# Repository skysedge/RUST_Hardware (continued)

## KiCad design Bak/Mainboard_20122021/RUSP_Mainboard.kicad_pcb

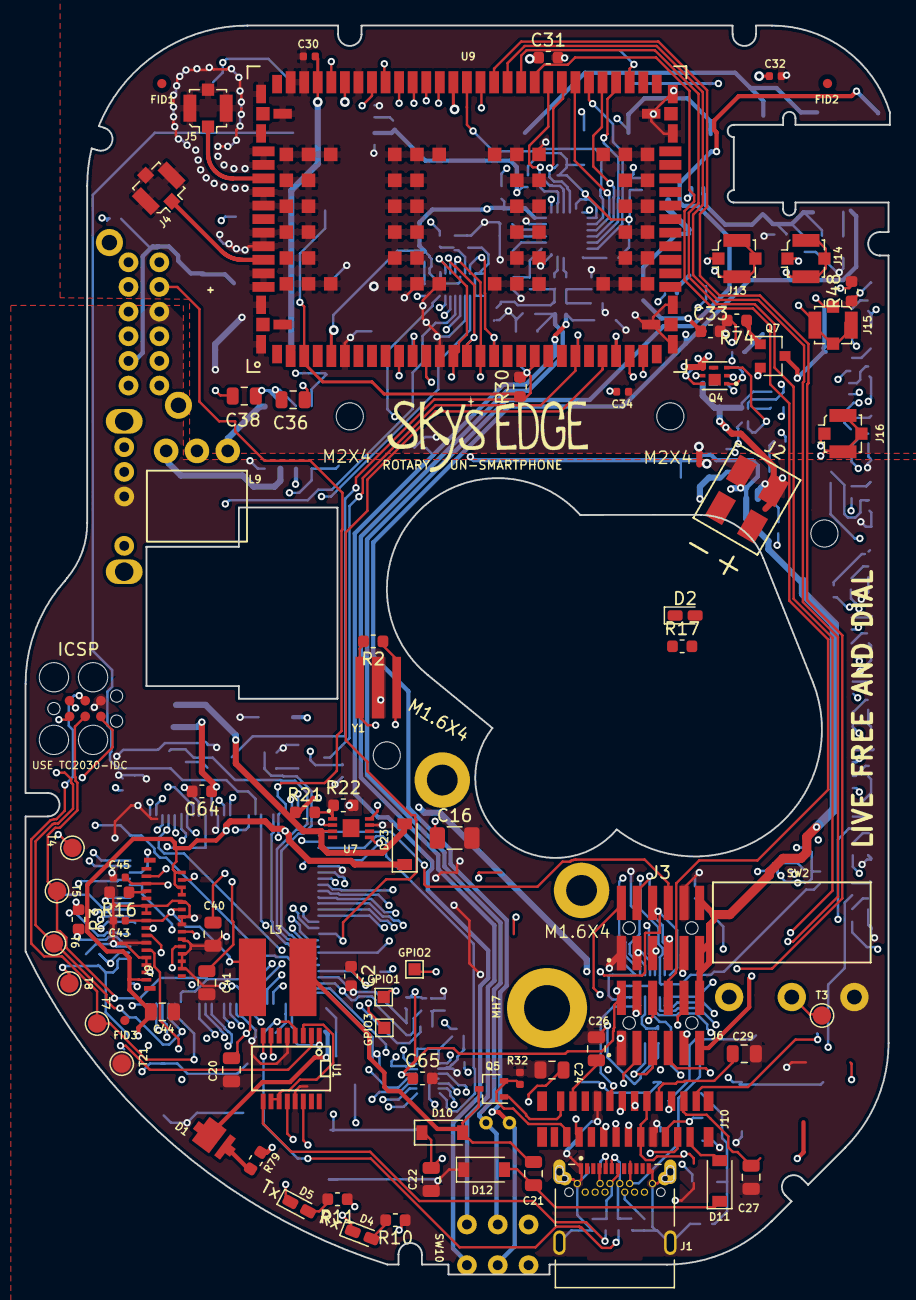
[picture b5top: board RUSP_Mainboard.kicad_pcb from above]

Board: 6 copper layers, 70.1 x 101.3 mm, 257 parts (0 on the bottom side), 234 nets.

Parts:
C1, C46, C47, C62, C63: 27pF; C_0603_1608Metric
C2, C3, C4, C5, C6, C10, C11, C18, C19, C39, C42, C56, C64, C65: .1uF; C_0603_1608Metric
C7, C48, C49, C60, C61: 10nF; C_0402_1005Metric
C8, C9: 47pF; C_0603_1608Metric
C12, C13: 4.7uF; C_0603_1608Metric
C14, C37: 100uF, 10V; Capacitor_Wurth865080243007
C15, C72: 2.2uF, LOW-ESR CER.; C_0603_1608Metric
C16, C17, C57: 10uF/35V; R_1206_3216Metric
C20, C21, C22, C41, C44: 4.7uF/25V; C_0805_2012Metric
C23, C24, C25, C26, C27, C28, C29: 1uF/50V; C_0805_2012Metric
C30: 68pF/50V; C_0402_1005Metric
C31: 15pF/50V; C_0603_1608Metric
C32: 8.2pF/50V; C_0402_1005Metric
C33: 10nF/16V; C_0603_1608Metric
C34: 100nF/16V; C_0402_1005Metric
C35: 330uF/6.3V, TANTALUM 45mR; C_2917
C36, C38, C40: 1uF/16V; C_0805_2012Metric
C43, C45, C51, C52, C53, C55, C58, C59: 1uF; C_0402_1005Metric
C50, C54: 2.2uF; C_0603_1608Metric
D1: LED; Osram_1212
D2, D5, D22: LED; LED_0603_1608Metric_Castellated
D3: D_Schottky; D_SOD-123
D4: RX/GREEN; LED_0603_1608Metric_Castellated
D10, D11, D12: MBR0530; D_SOD-123
D15, D16, D17, D18: TVS; R_0603_1608Metric_Pad1.05x0.95mm_HandSolder
D23: PMEG2005; D_SOD-123
D25, D26, D27, D28, D29, D30, D31, D32, D33, D34: R/Y; LED_Dialight_5988560207F
FID1, FID2, FID3, FID4, FID5, FID6: Fiducial; Fiducial_0.75mm_Dia_1.5mm_Outer
GPIO1, GPIO2, GPIO3, GPIO4: TestPoint_Alt; TestPoint_Pad_1.0x1.0mm
J1: USB_C_Receptacle; CUI_UJ31-CH-G1-SMT-TR
J2: IDC; AVX_PokeInConnector
J3, J6: Conn_01x12; Samtec_2x6Header_FTSH-106-01-L-DV
J4, J5, J13, J14, J15, J16: U.FL; U.FL_Molex_MCRF_73412-0110_Vertical
J7: Conn_02x03_Counter_Clockwise; Tag-Connect_TC2030-IDC
J8: AudioJack_TRRS_3Switch; AudioJack_TRRS_CUI_SJ-43617-SMT-TR
J9: FPC; Hirose_FPC_FH26W-31S-0.3SHW(60)
J10: FPC; Molex_24pFPC_Vert_0525592452
J11, J12: Conn_01x02; 2pSocket_SMD_Samtec_SMM-102-02-S-S
L1: Ferrite_Bead; R_0805_2012Metric_Pad1.15x1.40mm_HandSolder
L2: 4.7uH; Inductor_Wurth_74438336100
L3: 10uH; Inductor10uH_Wurth_744053100
L5, L6, L7, L8: EMI; L_0402_1005Metric
L9: COIL; 3pSocket_RA_GCT_BG302-03-A-L-G
LOGO1: Logo1; SkysEdge_21mm
LOGO2: Logo2; SkysEdge_18mm
LS1: Speaker; Speaker_PUI_AR01232MS-SC12-WP-R
MH1, MH3, MH4, MH8: MountingHole; MountingHole_2.2mm_M2
MH7: MountingHole; SMTSO-M2-3ET
MH9, MH10: MountingHole; SMTSO-M1.6-1ET
MK1: 2k2 Electret; Microphone_PUI_POM-2738P-R
NT2: Net-Tie_2; NetTie-2_SMD_Pad0.5mm
Q1, Q2: DMG2302UK-7; SOT-23
Q3, Q4: Q_NMOS_POWER; TI_CSD16301Q2
Q5: NMOS; SOT-323_SC-70
Q6, Q7: MMBT3904; SOT-23
R1, R29, R33, R39, R42, R66, R75, R76: 10k; R_0603_1608Metric
R2, R23, R24, R34, R41, R73: 1M; R_0603_1608Metric
R3, R6, R7: 27R; R_0603_1608Metric
R4, R5: 5k1; R_0402_1005Metric
R8, R9, R10, R11, R67, R74, R77, R78: 1k; R_0603_1608Metric
R12: 330R; R_0603_1608Metric
R13, R14, R35, R38: 2k2; R_0402_1005Metric
R15: 10R; R_0603_1608Metric
R16: 510k; R_0603_1608Metric
R17, R45, R46, R47, R48, R49, R50, R51, R52, R53, R54, R55, R56, R57, R58, R59, R60, R61, R62, R63, R64: 1k5; R_0603_1608Metric
R19, R20, R40, R65: 100R; R_0603_1608Metric
R21: 1.05M; R_0603_1608Metric
R22: 120k; R_0603_1608Metric
R26, R27, R30: 100k; R_0603_1608Metric
R31: 16k; R_0603_1608Metric
R32: 0.47R; R_0402_1005Metric
R36, R37: 4k7; R_0603_1608Metric
R44: 160R*; R_0603_1608Metric
R79: 18R; R_0603_1608Metric
RSVD1: TestPoint_Alt; TestPoint_Pad_1.0x1.0mm
SW1: SP3T; SP3T_OS103011MA7QP1
SW2: ROTARY DIAL ROLLER SWITCH; LimitSwitch_D2F-01FL2-A1
SW3, SW4, SW5, SW6, SW7, SW8: Tactile Switch; TactileSwitch_Panasonic_EVQ-Q2Y03W
SW9: SW_4P2T; Switch_4PDT_ESwitch-EG4208
SW10: SW_DPDT; Switch_DPDT_Nidec_CL-SB-22C-XX
T2, T9, T10, T11, T12, T13, T14, T15, T16, T17, T18, T19, T20: TestPoint_Alt; TestPoint_Pad_1.0x1.0mm
T3, T4, T5, T6, T7, T8, T21: TestPoint_Alt; TestPoint_Pad_D1.5mm
U1: FT230XS; SSOP-16
U2, U8, U10: TXB0108DQS; USON-20_2x4mm_P0.4mm
U3: BQ29703DSET; WSON-6_1.5x1.5mm_P0.5mm
U4: ATmega2560V-8AU; TQFP-100_14x14mm_P0.5mm
U5: MCP73831-2-OT; SOT-23-5
U6: MIC5528; LDO_MIC5528
U7: MCP1661; BoostConverter_MCP1661
U9: TOBY-L2; CellModule_TOBY-L2
U11: ZXBM5210-SP-13; SO-8EP
U12: MAX9860; WQFN-24-1EP_4x4mm_P0.5mm_EP2.7x2.7mm
Y1: 8MHz; AWSCR-16.00CV-T

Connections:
+1V8: C39.1, C56.1, C57.1, C58.1, C59.1, J6.11, R36.1, R37.1, R39.1, T12.1, U9.5, U10.1, U10.5, U12.6, U12.11, U12.13
+3V3: C19.1, C20.2, C43.2, C65.1, C72.2, J6.2, J9.12, J9.15, J10.15, J10.16, L3.1, U2.5, U6.1, U6.2, U8.5
+3V8: C3.1, C4.1, C5.1, C6.1, C15.2, C16.1, C18.1, C30.1, C31.1, C32.1, C33.1, C34.1, C35.1, C42.1, C64.1, J3.2, J3.3, J7.2, L2.1, R1.2, R10.1, R11.1, R15.2, R26.1, R27.1, R79.2, T4.1, U1.12, U2.16, U4.10, U4.31, U4.61, U4.80, U4.100, U6.6, U7.5, U8.16, U9.70, U9.71, U9.72, U10.16
+12V: C17.1, C36.1, C38.2, C44.1, D23.1, J9.2, J9.6, J9.8, J9.31, R21.1, U11.2, U11.3, U11.6
+BATT: C13.2, J2.2, J3.11, J3.12, J6.12, R12.1, SW9.2, U5.3
/3v3_EN: R19.2, U4.56
/12v_EN: U4.57, U7.8
/AREF: C2.1, U4.98
/AUDIO/BLCK: U9.52, U12.18
/CELL MODEM/ANT1: J5.1, U9.81
/CELL MODEM/ANT2: J4.1, U9.87
/CELL MODEM/CTS_1v8: T17.1, U9.15, U10.3
/CELL MODEM/DCD_1v8: T9.1, U9.12
/CELL MODEM/DSR_1v8: T2.1, U9.10
/CELL MODEM/HOST_SELECT0: T10.1, U9.26
/CELL MODEM/HOST_SELECT1: T11.1, U9.62
/CELL MODEM/I2S_GPIO6: U9.61, U12.14
/CELL MODEM/I2S_RXD: U9.53, U12.15
/CELL MODEM/I2S_SCL: R37.2, U9.54, U12.10
/CELL MODEM/I2S_SDA: R36.2, U9.55, U12.9
/CELL MODEM/I2S_TXD: U9.51, U12.16
/CELL MODEM/I2S_WA: U9.50, U12.17
/CELL MODEM/RI_1v8: U9.11, U10.8
/CELL MODEM/RTS_1v8: T16.1, U9.14, U10.2
/CELL MODEM/RXD_1v8: T19.1, U9.17, U10.7
/CELL MODEM/SDIO-CLK: J14.1, U9.64
/CELL MODEM/SDIO-CMD: J14.2, U9.65
/CELL MODEM/SDIO-D0: J13.1, U9.66
/CELL MODEM/SDIO-D1: J13.2, U9.68
/CELL MODEM/SDIO-D2: J15.1, U9.63
/CELL MODEM/SDIO-D3: J15.2, U9.67
/CELL MODEM/TXD_1v8: T18.1, U9.16, U10.4
/CELL MODEM/USB_D+: J16.1, U9.28
/CELL MODEM/USB_D-: J16.2, U9.27
/CELL MODEM/V_BCKP: C37.1, R30.1, U9.3
/CELL_CTS: U4.94, U10.18
/CELL_ON: R41.1, R65.2, U4.97
/CELL_PWR_DET: U4.95, U10.20
/CELL_RESET: R34.1, R40.2, U4.96
/CELL_RI: U4.18, U10.13
/CELL_RTS: U4.93, U10.19
/CELL_RXD: U4.45, U10.14
/CELL_TXD: U4.46, U10.17
/EPD_BUSY: J10.9, U4.71
/EPD_CS: R26.2, U4.75, U8.18
/EPD_DC: U4.74, U8.17
/EPD_RESET: R27.2, U4.72, U8.14
/GPIO1: GPIO1.1, U4.5
/GPIO2: GPIO2.1, U4.6
/GPIO3: GPIO3.1, U4.7
/GPIO4: GPIO4.1, U4.39
/LED_1A: R49.2, U4.17
/LED_1B: R50.2, U4.16
/LED_2A: R51.2, U4.15
/LED_2B: R52.2, U4.13
/LED_3A: R53.2, U4.12
/LED_3B: R54.2, U4.52
/LED_4A: R45.2, U4.42
/LED_4B: R46.2, U4.91
/LED_5A: R63.2, U4.90
/LED_5B: R64.2, U4.89
/LED_6A: R61.2, U4.88
/LED_6B: R62.2, U4.87
/LED_7A: R59.2, U4.86
/LED_7B: R60.2, U4.85
/LED_8A: R57.2, U4.83
/LED_8B: R58.2, U4.82
/LED_9A: R55.2, U4.63
/LED_9B: R56.2, U4.51
/LED_10A: R47.2, U4.64
/LED_10B: R48.2, U4.84
/LED_BELL: R78.2, U4.1
/LED_FILAMENT: R74.2, U4.38
/LED_STAT: R44.2, U4.37
/MCURX-TO-FTDITX: R8.2, U4.2
/MCUTX-TO-FTDIRX: R9.1, U4.3
/MISO: J3.5, J7.1, T6.1, U4.22
/MOSI: J3.4, J7.4, T7.1, U2.14, U4.21, U8.19
/NET_STAT: U4.92, U9.25
/OFFSIGNAL: SW9.8, U4.73
/OLED DRIVER/OLED_CS_3V3: J9.17, U2.1
/OLED DRIVER/OLED_D0-SCL_3V3: J9.22, U2.4
/OLED DRIVER/OLED_D1-MOSI_3V3: J9.23, U2.7
/OLED DRIVER/OLED_DC_3V3: J9.19, U2.3
/OLED DRIVER/OLED_IREF: J9.7, R16.1
/OLED DRIVER/OLED_RES_3V3: J9.18, U2.2
/OLED DRIVER/OLED_VCOMH: C41.1, J9.4
/OLED DRIVER/OLED_VLOGIC: C45.2, J9.5
/OLED DRIVER/OLED_VP: C40.1, J9.3
/OLED_CS: U2.20, U4.78
/OLED_DC: U2.18, U4.54
/OLED_XRES: U2.19, U4.53
/PDn: J6.10, U4.8
/POWSW4: J3.9, SW9.4
/RELAY_OFF: J6.4, U4.55
/RESET: C1.1, C10.1, J7.5, R1.1, T8.1, U4.30
/RINGER+: R23.1, U4.43, U11.4
/RINGER-: R24.1, U4.44, U11.5
/SCK: J3.6, J7.3, T5.1, U2.17, U4.20, U8.20
/SD_CD: J3.7, U4.77
/SD_CS: J3.8, U4.76
/SIM_CLK: J6.8, U9.56
/SIM_IO: J6.9, U9.57
/SIM_RST: J6.7, U9.58
/SW_CLEAR: SW4.1, U4.67
/SW_HOOK: SW7.1, U4.68
/SW_MODE1: SW1.4, U4.58
/SW_MODE2: SW1.3, U4.59
/SW_MODE3: SW1.1, U4.60
/SW_MULTI1: SW3.1, U4.23
/SW_MULTI2: SW6.1, U4.25
/SW_MULTI3: SW5.1, U4.24
/SW_MULTI4: SW8.1, U4.26
/SW_ROTARY: SW2.2, T3.1, U4.69
/VSIM: J6.6, U9.59
/ePaper Driver/CS_3v3: J10.12, U8.3
/ePaper Driver/DC_3v3: J10.11, U8.4
/ePaper Driver/GDR: J10.2, Q5.1
/ePaper Driver/MOSI_3v3: J10.14, U8.2
/ePaper Driver/PREVGH: C22.2, D10.1, J10.21
/ePaper Driver/PREVGL: D11.2, J10.23
/ePaper Driver/RESE: J10.3, Q5.2, R32.1
/ePaper Driver/RESET_3v3: J10.10, U8.7
/ePaper Driver/SCK_3v3: J10.13, U8.1
/ePaper Driver/VCOM: C28.1, J10.24
/ePaper Driver/VDD: C29.1, J10.18
/ePaper Driver/VGH: C24.1, J10.5
/ePaper Driver/VGL: C26.1, J10.4
/ePaper Driver/VPP: C25.1, J10.19
/ePaper Driver/VSH: C23.1, J10.20
/ePaper Driver/VSL: C27.1, J10.22
GND: C1.2, C2.2, C3.2, C4.2, C5.2, C6.2, C7.2, C8.2, C9.2, C12.2, C13.1, C14.2, C15.1, C16.2, C17.2, C18.2, C19.2, C20.1, C22.1, C23.2, C24.2, C25.2, C26.2, C27.2, C28.2, C29.2, C36.2, C38.1, C40.2, C41.2, C43.1, C44.2, C45.1, C56.2, C57.2, C58.2, C59.2, C64.2, C65.2, C72.1, D2.1, D12.1, D22.1, D25.2, D25.4, D26.2, D26.4, D27.2, D27.4, D28.2, D28.4, D29.2, D29.4, D30.2, D30.4, D31.2, D31.4, D32.2, D32.4, D33.2, D33.4, D34.2, D34.4, J1.A1, J1.A12, J1.B1, J1.B12, J1.S1, J3.1, J3.10, J6.1, J7.6, J9.10, J9.11, J9.13, J9.14, J9.16, J9.20, J9.21, J9.24, J9.25, J9.26, J9.27, J9.28, J9.29, J10.8, J10.17, NT2.1, Q1.2, Q2.2, Q4.4, Q6.2, Q7.2, R4.2, R5.2, R13.1, R14.1, R16.2, R22.2, R23.2, R24.2, R32.2, R34.2, R41.2, R42.2, R66.2, R73.1, R75.2, R76.2, SW1.2, SW2.1, SW3.2, SW4.2, SW5.2, SW6.2, SW7.2, SW8.2, SW9.9, T21.1, U1.5, U1.13, U2.15, U4.11, U4.32, U4.62, U4.81, U4.99, U5.2, U6.3, U7.2, U7.7, U8.15, U11.8, U12.12, Y1.2
GNDA: C30.2, C31.2, C32.2, C33.2, C34.2, C35.2, C37.2, C39.2, C42.2, C46.2, C47.2, C48.2, C49.2, C50.2, C53.2, C54.2, C55.2, C60.2, C61.2, C62.2, C63.2, D15.2, D16.2, D17.2, D18.2, J4.2, J5.2, NT2.2, R29.2, R33.2, R35.2, T20.1, U9.2, U9.6, U9.13, U9.30, U9.32, U9.44, U9.46, U9.69, U9.73, U9.74, U9.76, U9.78, U9.79, U9.80, U9.82, U9.83, U9.85, U9.86, U9.88, U9.89, U9.90, U9.92, U9.93, U9.94, U9.95, U9.96, U9.97, U9.98, U9.99, U9.100, U9.101, U9.102, U9.103, U9.104, U9.105, U9.106, U9.107, U9.108, U9.109, U9.110, U9.111, U9.112, U9.113, U9.114, U9.115, U9.116, U9.117, U9.118, U9.119, U9.120, U9.121, U9.122, U9.123, U9.124, U9.125, U9.126, U9.127, U9.128, U9.129, U9.130, U9.131, U9.132, U9.133, U9.134, U9.135, U9.136, U9.137, U9.138, U9.139, U9.140, U9.141, U9.142, U9.143, U9.144, U9.145, U9.146, U9.147, U9.148, U9.149, U9.150, U9.151, U9.152, U10.15, U12.5, U12.24
LL_OE: J6.5, R31.2, R67.2, R77.2, U4.50
unnamed: C7.1, D3.1, L1.1
unnamed: C8.1, J1.A7, J1.B7, R7.2
unnamed: C9.1, J1.A6, J1.B6, R6.2
unnamed: C10.2, U1.2
unnamed: C11.1, R12.2, U3.5
unnamed: C11.2, J2.1, Q3.4, U3.4
unnamed: C14.1, R20.2, SW9.5
unnamed: C21.1, D11.1, D12.2
unnamed: C21.2, D10.2, L3.2, Q5.3
unnamed: C46.1, D15.1, L5.2, SW10.1
unnamed: C47.1, D16.1, L6.2, SW10.4
unnamed: C48.1, C51.2, L5.1, R35.1
unnamed: C49.1, C52.2, L6.1, R38.1
unnamed: C50.1, R38.2, U12.1
unnamed: C51.1, U12.22
unnamed: C52.1, U12.23
unnamed: C53.1, U12.3
unnamed: C54.1, U12.4
unnamed: C55.1, U12.2
unnamed: C60.1, C62.1, D17.1, J8.2, L7.1
unnamed: C61.1, C63.1, D18.1, J8.3, L8.1
unnamed: D1.1, Q6.3
unnamed: D1.2, R79.1
unnamed: D2.2, R17.1
unnamed: D3.2, J1.A4, J1.A9, J1.B4, J1.B9
unnamed: D4.1, U1.14
unnamed: D4.2, R10.2
unnamed: D5.1, U1.7
unnamed: D5.2, R11.2
unnamed: D22.2, R44.1
unnamed: D23.2, L2.2, U7.3
unnamed: D25.1, R45.1
unnamed: D25.3, R46.1
unnamed: D26.1, R47.1
unnamed: D26.3, R48.1
unnamed: D27.1, R49.1
unnamed: D27.3, R50.1
unnamed: D28.1, R51.1
unnamed: D28.3, R52.1
unnamed: D29.1, R53.1
unnamed: D29.3, R54.1
unnamed: D30.1, R55.1
unnamed: D30.3, R56.1
unnamed: D31.1, R57.1
unnamed: D31.3, R58.1
unnamed: D32.1, R59.1
unnamed: D32.3, R60.1
unnamed: D33.1, R61.1
unnamed: D33.3, R62.1
unnamed: D34.1, R63.1
unnamed: D34.3, R64.1
unnamed: J1.A5, R5.1
unnamed: J1.B5, R4.1
unnamed: J8.1, MK1.1, SW10.5
unnamed: J8.4, SW10.2
unnamed: J8.10, LS1.1
unnamed: J8.11, LS1.2
unnamed: J8.12, MK1.2
unnamed: J11.1, J11.2, R15.1
unnamed: J12.1, J12.2, Q7.3
unnamed: L7.2, U12.7
unnamed: L8.2, U12.8
unnamed: L9.1, U11.1
unnamed: L9.2, U11.7
unnamed: Q1.1, R40.1
unnamed: Q1.3, T15.1, U9.23
unnamed: Q2.1, R65.1
unnamed: Q2.3, R30.2, T14.1, U9.20
unnamed: Q3.1, Q4.1
unnamed: Q3.2, Q4.2
unnamed: Q3.3, U3.3
unnamed: Q3.5, Q4.5
unnamed: Q3.6, Q4.6
unnamed: Q4.3, U3.2
unnamed: Q6.1, R78.1
unnamed: Q7.1, R74.1
unnamed: R2.1, R3.1, Y1.3
unnamed: R2.2, U4.34, Y1.1
unnamed: R3.2, U4.33
unnamed: R6.1, U1.8
unnamed: R7.1, U1.9
unnamed: R8.1, U1.1
unnamed: R9.2, U1.4
unnamed: R13.2, U3.6
unnamed: R14.2, U5.5
unnamed: R17.2, U5.1
unnamed: R19.1, R73.2, U6.4
unnamed: R20.1, SW9.3
unnamed: R21.2, R22.1, U7.1
unnamed: R29.1, R31.1, U10.6
unnamed: R33.1, U10.9, U10.10, U10.11, U10.12
unnamed: R39.2, U12.19
unnamed: R42.1, U2.8, U2.9, U2.10, U2.11, U2.12, U2.13
unnamed: R66.1, R67.1, U2.6
unnamed: R75.1, U8.8, U8.9, U8.10, U8.11, U8.12, U8.13
unnamed: R76.1, R77.1, U8.6
unnamed: RSVD1.1, U9.49
unnamed: T13.1, U9.60
unnamed: U1.3, U1.10, U1.11
VBUS: C12.1, J6.3, L1.2, U5.4

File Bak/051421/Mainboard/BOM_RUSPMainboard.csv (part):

C1,22pF,Capacitor_SMD:C_0402_1005Metric,,,399-9031-1-ND ,Digi-Key,,,Kemet,C0402C220J5GACTU,,,1
">  C2-C6, C10, C11, C18, C19, C39, C42, C56, C64, C65",.1uF,Capacitor_SMD:C_0402_1005Metric,...,,...,...,,...,Kemet,C0402C104Z4VACTU,,,14
    C7,10nF,Capacitor_SMD:C_0402_1005Metric,,,1276-1009-1-ND ,Digi-Key,,50V,Kemet,C0402C103K4RACTU,,,1
">  C8, C9",47pF,Capacitor_SMD:C_0402_1005Metric,,,399-7918-1-ND ,Digi-Key,,,Kemet,C0402C470K5GACTU,,,2
">  C12, C13",4.7uF,Capacitor_SMD:C_0603_1608Metric,~,,,,,,Samsung,CL10A475KQ8NNNC,,,2
">  C14, C37",...,...,https://www.we-online.de/katalog/datasheet/865080243007.pdf,,,,...,,Wurth,8.6508E+11,,,2
">  C15, C72","2.2uF, LOW-ESR CER.",Capacitor_SMD:C_0402_1005Metric,~,,,,,,TDK,C1005X5R1A225M050BC,,X5R or X7R,2
    C16,10uF/10V,Capacitor_SMD:C_0805_2012Metric,~,,,,,,TDK,C2012X7R1A106K125AC,,,1
    C17,10uF/35V,Resistor_SMD:R_1206_3216Metric,~,,,,,,TDK,CGA5L1X7R1V106K160AC,,,1
>  C20-C22,4.7uF/25V,Capacitor_SMD:C_0805_2012Metric,~,,,,,,Samsung,CL21A475KBQNNNE,,,3
>  C23-C29,1uF/50V,Capacitor_SMD:C_0805_2012Metric,~,,,,,,Yageo,CC0805KKX7R9BB105,,,7
    C30,68pF/50V,Capacitor_SMD:C_0402_1005Metric,~,,,,,,Murata,GRM1555C1H680JA01J,,,1
    C31,15pF/50V,Capacitor_SMD:C_0402_1005Metric,~,,,,,,Murata,GRM1555C1H150JA01J,,,1
    C32,8.2pF/50V,Capacitor_SMD:C_0402_1005Metric,~,,,,,,Yageo,CC0402DRNPO9BN8R2,,,1
    C33,10nF/16V,Capacitor_SMD:C_0402_1005Metric,~,,,,,,Murata,GRM155R71C103KA01D,,,1
    C34,100nF/16V,Capacitor_SMD:C_0402_1005Metric,~,,,,,,Kemet,C0402C104K4RACTU,,,1
    C35,"330uF/6.3V, TANTALUM 45mR",MyFootprints:C_2917,~,,,,,,Kemet,T520D337M006ATE045,,,1
">  C46, C47, C62, C63",27pF,Capacitor_SMD:C_0402_1005Metric,~,,,,,,Kemet,C0402C270J5GACTU,,,4
">  C48, C49, C60, C61",10nF,Capacitor_SMD:C_0402_1005Metric,~,,,,,,Murata,GCM155R71H103KA55D ,,,4
">  C50, C54",2.2uF,Capacitor_SMD:C_0603_1608Metric,~,,,,,,Kemet,C0603C225K9PACTU,,,2
">  C51-C53, C55, C58, C59",1uF,Capacitor_SMD:C_0402_1005Metric,~,,,,,,Kemet,C0402C105K9PACTU,,,6
    C57,10uF,Capacitor_SMD:C_0603_1608Metric,~,,,,,,Kemet,C0603C106M9PACTU,,,1
">  C66, C67",.1uF/X7R/+-10%,Capacitor_SMD:C_0603_1608Metric,~,,,,,,Kemet,C0603C104K3RACTU,,,2
>  C68-C71,4.7uF/25V,Capacitor_SMD:CP_Elec_4x4.5,~,,,,,,Wurth,8.65081E+11,,,4
    D3,D_Schottky,Diode_SMD:D_SOD-123,~,,MBR130T3GOSCT-ND,DigiKey,,,ON Semiconductor,MBR130T3G,,,1
    D4,RX/GREEN,LED_SMD:LED_0603_1608Metric_Castellated,,Rx/GREEN,475-3442-1-ND?,DigiKey,,,OSRAM,LT Q39G-Q1OO-25-1,,,1
">  D5, D21",...,LED_SMD:LED_0603_1608Metric_Castellated,,...,...,DigiKey,,,Inolux,IN-S63AT5Y,,,2
>  D10-D12,MBR0530,Diode_SMD:D_SOD-123,http://www.mccsemi.com/up_pdf/MBR0520~MBR0580(SOD123).pdf,,,,,,ON Semi,MBR0530,,,3
>  D15-D18,TVS,Resistor_SMD:R_0603_1608Metric_Pad1.05x0.95mm_HandSolder,~,,,,,,AVX,USB0001DP ,,,4
    D22,LED,LED_SMD:LED_0603_1608Metric_Castellated,,TEAL,,,,,Rohm,SMLE13EC8TT86,,,1
    D23,PMEG2005,Diode_SMD:D_SOD-123,https://assets.nexperia.com/documents/data-sheet/PMEG2005EGW.pdf,,,,,,Nexperia,PMEG2005EGWJ ,,,1
    D24,1N4148,Diode_SMD:D_SOD-123,,,,,,,Diodes Incorporated, 1N4148W-13-F,,,1
>  D25-D34,R/Y,MyFootprints:LED_Dialight_5988560207F,http://www.dialightsignalsandcomponents.com/Assets/Brochures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,,,,,,Dialight,5988560207F,,,10
>  FID1-FID6,Fiducial,Fiducial:Fiducial_0.75mm_Dia_1.5mm_Outer,,,,,,,,,,,6
>  GPIO1-GPIO4,TestPoint_Alt,TestPoint:TestPoint_Pad_1.0x1.0mm,~,,,,,,,,,,4
    J1,USB_C_Receptacle,digikey-footprints:CUI_UJ31-CH-G1-SMT-TR,https://www.cuidevices.com/product/resource/uj31-ch-g1-smt-tr.pdf,,,,,,CUI,UJ31-CH-G1-SMT-TR,,,1
    J2,JST2,MyFootprints:S2B-PH-SM4-TBLFSN,~,,455-1749-1-ND,DigiKey,S2B-PH-SM4-TB(LF)(SN),,JST,S2B-PH-SM4-TB(LF)(SN),,,1
    J3,Conn_01x12,MyFootprints:Samtec_2x6Header_FTSH-106-01-L-DV,~,,,,,,Samtec,FTSH-106-01-L-DV,,,1
">  J4, J5",U.FL,Connector_Coaxial:U.FL_Molex_MCRF_73412-0110_Vertical, ~,,,,,,Molex,734120110,,,2
    J6,Conn_01x12,MyFootprints:Samtec_2x6Header_FTSH-106-01-L-DV,~,,,,,,Samtec,FTSH-106-01-L-DV ,,,1
    J7,Conn_02x03_Counter_Clockwise,MyFootprints:Tag-Connect_TC2030-IDC,~,,,,,ICSP,Tag-Connect,Mating Connector: TC2030-IDC ,,,1
    J8,AudioJack_TRRS_3Switch,MyFootprints:AudioJack_TRRS_CUI_SJ-43617-SMT-TR,,,,,,TRRS JACK,CUI,SJ-43617-SMT-TR,,,1
    J9,FPC,MyFootprints:Hirose_FPC_FH26W-31S-0.3SHW(60),~,,,,,,Hirose,FH26W-31S-0.3SHW(60),,,1
    J10,FPC,MyFootprints:Molex_24pFPC_Vert_0525592452,~,,,,,,Molex,525592452,,,1
">  J11, J12",Conn_01x02,MyFootprints:2pSocket_SMD_Samtec_SMM-102-02-S-S,~,,,,,,Samtec,SMM-102-02-S-S,,,2
    L1,Ferrite_Bead,Resistor_SMD:R_0805_2012Metric_Pad1.15x1.40mm_HandSolder,,,240-2390-1-ND,DigiKey,,,Laird,MI0805K601R-10,,,1
    L2,4.7uH,MyFootprints:Inductor_Wurth_74438336100,https://www.we-online.de/katalog/datasheet/74438336100.pdf,,,,,,Wurth,74438336047,,,1
    L3,10uH,MyFootprints:Inductor10uH_Wurth_744053100,~,,,,,,Wurth,744053100,,,1
>  L5-L8,EMI,Inductor_SMD:L_0402_1005Metric,~,,,,,,Murata,BLM15HD182SN1D,,,4
    L9,COIL,MyFootprints:3pSocket_RA_GCT_BG302-03-A-L-G,,,,,,,GCT,BG302-03-A-L-G,,Bourns RLB9012-472KL,1
">  LOGO1, LOGO2",...,...,~,,,,,,,,,,2
    LS1,Speaker,MyFootprints:Speaker_PUI_AR01232MS-SC12-WP-R,http://www.puiaudio.com/pdf/AR01232MS-SC12-WP-R.pdf,,,,,,PUI Audio,AR01232MS-SC12-WP-R,,,1
">  MH1-MH4, MH8",MountingHole,MountingHole:MountingHole_2.2mm_M2,~,,,,,,,,,,5
">  MH5, MH6, MH9, MH10",MountingHole,MyFootprints:SMTSO-M1.6-1ET,~,,,,,,PEM,SMTSO-M1.6-1ET,,,4
    MH7,MountingHole,MyFootprints:SMTSO-M2-3ET,~,,,,,,PEM,SMTSO-M2-3ET,,,1
    MK1,2k2 Electret,MyFootprints:Microphone_PUI_POM-2738P-R,http://www.puiaudio.com/pdf/POM-2738P-R.pdf,,,,,,PUI Audio,POM-2738P-R,,,1
    NT2,Net-Tie_2,NetTie:NetTie-2_SMD_Pad0.5mm,~,,,,,,,,,,1
">  Q1, Q2, Q6",DMG2302UK-7 ,Package_TO_SOT_SMD:SOT-23,https://www.diodes.com/assets/Datasheets/DMG2302UK.pdf,,,,,,Diodes Incorporated,DMG2302UK-7,,,3
">  Q3, Q4",Q_NMOS_POWER,digikey-footprints:TI_CSD16301Q2,,,,,,,TI,CSD16301Q2,,,2
    Q5,NMOS,Package_TO_SOT_SMD:SOT-323_SC-70,https://www.vishay.com/docs/63399/si1308edl.pdf,,,,,,Vishay,SI1308EDL-T1-GE3 ,,,1
    Q7,MMBT3904,Package_TO_SOT_SMD:SOT-23,https://www.fairchildsemi.com/datasheets/2N/2N3904.pdf,,,,,,Fairchild,MMBT3904,,,1
">  R1, R29, R33, R39, R42, R66, R68-R71, R75, R76",10k,Resistor_SMD:R_0402_1005Metric,...,,,,,,TE,CRGCQ0402J10K,,,12
">  R2, R24, R34, R41, R73",1M,Resistor_SMD:R_0402_1005Metric,...,,...,...,,,Yageo,RC0402FR-071ML,,,5
">  R3, R6, R7",27R,Resistor_SMD:R_0402_1005Metric,,,RMCF0603JT27R0CT-ND ,Digi-Key,,,Panasonic,ERJ-2GEJ270X,,,3
">  R4, R5",5k1,Resistor_SMD:R_0402_1005Metric,~,,,,,,Yageo,RC0402FR-075K1L,,,2
">  R8-R11, R74",1k,Resistor_SMD:R_0402_1005Metric,...,,...,...,,,Yageo,RC0402JR-071KL,,,5
    R12,330R,Resistor_SMD:R_0402_1005Metric,~,,,,,,Panasonic,ERJ-2GEJ331X,,,1
">  R13, R14, R35, R38",2k2,Resistor_SMD:R_0402_1005Metric,~,,,,,...,Panasonic,ERJ-2GEJ222X,,,4
    R15,10R,Resistor_SMD:R_0603_1608Metric,,,,,,,Panasonic,ERJ-3GEYJ100V,,,1
    R18,470R,Resistor_SMD:R_0402_1005Metric,~,,,,,,Yageo,RC0402JR-07470RL,,,1
">  R19, R20, R23, R40, R65",100R,Resistor_SMD:R_0402_1005Metric,~,,,,,,Panasonic,ERJ-2RKF1000X,,,5
    R21,1.05M,Resistor_SMD:R_0402_1005Metric,~,,,,,,Yageo,RC0402FR-071M05L,,,1
    R22,120k,Resistor_SMD:R_0402_1005Metric,~,,,,,,Yageo,RC0402FR-07120KL,,,1
">  R16, R17, R25, R28",0R,Resistor_SMD:R_0603_1608Metric,~,,,,,,,,,,4
">  R26, R27, R30",100k,Resistor_SMD:R_0402_1005Metric,~,,,,,,Yageo,RC0402FR-07100KL,,,3
    R31,16k,Resistor_SMD:R_0402_1005Metric,~,,,,,,Yageo,RC0402FR-0716KL,,,1
    R32,0.47R,Resistor_SMD:R_0402_1005Metric,~,,,,,,Panasonic,ERJ-2BQJR47X,SETS COMPATIBILITY FOR GDEW029I6F,,1
">  R36, R37",4k7,Resistor_SMD:R_0402_1005Metric,~,,,,,,TE,CRG0402F4K7,,,2
    R44,160R,Resistor_SMD:R_0402_1005Metric,,,,,,,Yageo,RC0402FR-07160RL,,,1
">  R43, R45-R64",1k5,Resistor_SMD:R_0402_1005Metric,,,A130092CT-ND,Digi-Key,,,Yageo,RC0402FR-071K5L,,,21
">  R67, R77",2k,Resistor_SMD:R_0402_1005Metric,~,,,,,,Yageo,RC0402JR-072KL,,,2
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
